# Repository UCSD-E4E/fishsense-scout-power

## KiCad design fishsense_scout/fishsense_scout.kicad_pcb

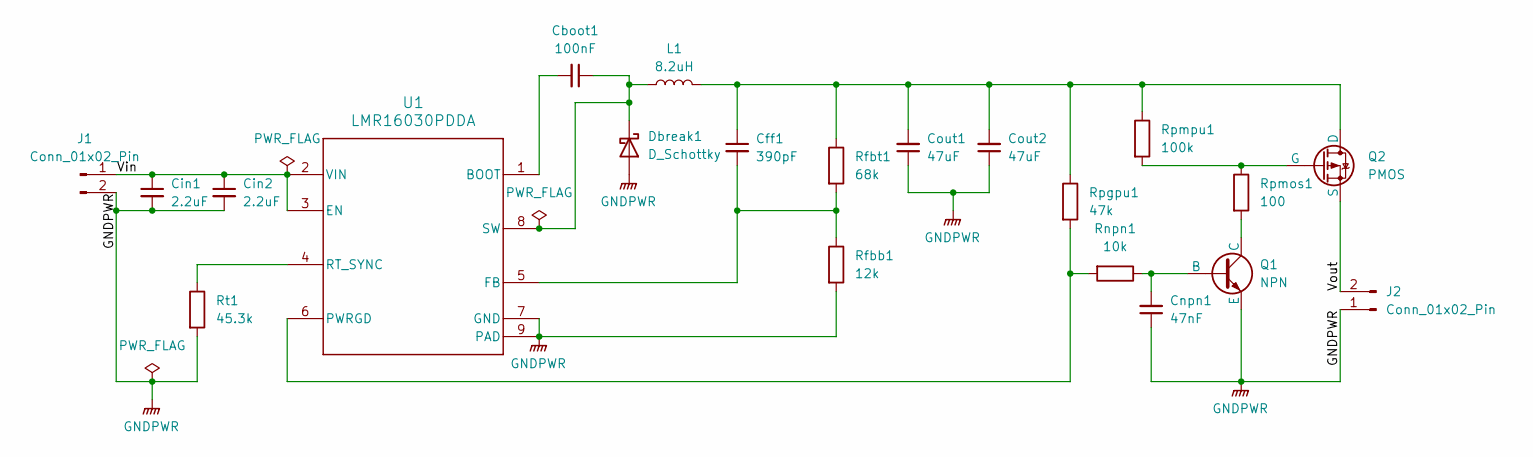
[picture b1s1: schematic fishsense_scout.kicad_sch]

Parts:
Cboot1: 100nF; C_0603_1608Metric
Cff1: 390pF; C_0603_1608Metric
Cin1, Cin2: 2.2uF; C_1210_3225Metric
Cnpn1: 47nF; C_0603_1608Metric
Cout1, Cout2: 47uF; C_1210_3225Metric
Dbreak1: D_Schottky; D_SMB
J1, J2: Conn_01x02_Pin; PinSocket_1x02_P2.54mm_Vertical
L1: 8.2uH; L_7.3x7.3_H3.5
Q1: NPN; SOT-23
Q2: PMOS; SOT-23
Rfbb1: 12k; R_0603_1608Metric
Rfbt1: 68k; R_0603_1608Metric
Rnpn1: 10k; R_0603_1608Metric
Rpgpu1: 47k; R_0603_1608Metric
Rpmos1: 100; R_0603_1608Metric
Rpmpu1: 100k; R_0603_1608Metric
Rt1: 45.3k; R_0603_1608Metric
U1: LMR16030PDDA; SOIC-8-1EP_3.9x4.9mm_P1.27mm_EP2.514x3.2mm_ThermalVias

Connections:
/Vin: Cin1.1, Cin2.1, J1.1, U1.2 (VIN), U1.3 (EN)
/Vout: J2.2, Q2.3 (S)
GNDPWR: Cin1.2, Cin2.2, Cnpn1.1, Cout1.1, Cout2.1, Dbreak1.2 (A), J1.2, J2.1, Q1.3 (E), Rfbb1.2, Rt1.2, U1.7 (GND), U1.9 (PAD)
unnamed: Cboot1.1, Dbreak1.1 (K), L1.1, U1.8 (SW)
unnamed: Cnpn1.2, Q1.2 (B), Rnpn1.1
unnamed: Q1.1 (C), Rpmos1.2
unnamed: Cff1.1, Cout1.2, Cout2.2, L1.2, Q2.1 (D), Rfbt1.1, Rpgpu1.1, Rpmpu1.1
unnamed: Q2.2 (G), Rpmos1.1, Rpmpu1.2
unnamed: Cboot1.2, U1.1 (BOOT)
unnamed: Cff1.2, Rfbb1.1, Rfbt1.2, U1.5 (FB)
unnamed: Rnpn1.2, Rpgpu1.2, U1.6 (PWRGD)
unnamed: Rt1.1, U1.4 (RT_SYNC)

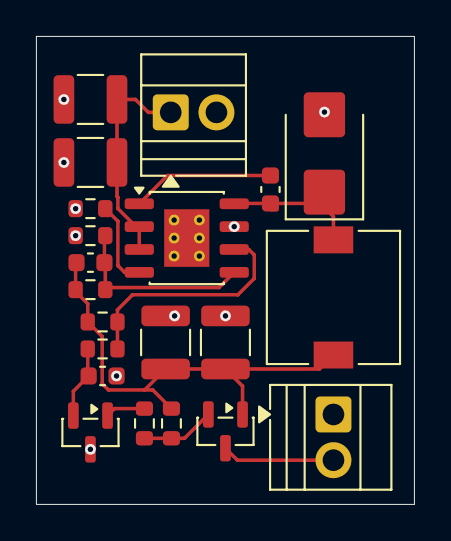
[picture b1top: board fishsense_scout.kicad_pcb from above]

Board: 2 copper layers, 21.0 x 26.0 mm, 21 parts (0 on the bottom side), 12 nets.

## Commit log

2026-03-11 add scout pcb files
2026-03-11 Added footprint and buck converter schematic to KiCad
2026-05-25 Finished PCB schematic design along with ERC check, assigned footprints, and made rough arrangement of components in PCB
2026-05-25 Small arrangementtweaks
2026-06-02 Added traces and rearranged footprints slightly to accomodate for traces
2026-06-03 Rearranged traces and added new pin connectors
2026-06-04 Changed pin headers into screw terminal blocks
